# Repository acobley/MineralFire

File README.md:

View this project on [CADLAB.io](https://cadlab.io/node/793). 

# Volca_Pulse

Software for MineralFire Eurorack module.

This is an Arduino based programmable clock divider.  

NOTES
The Most up to date branch is "AltCounter"

The hardware design is in testing, do not use for production. 

The Software works, but is still under development.

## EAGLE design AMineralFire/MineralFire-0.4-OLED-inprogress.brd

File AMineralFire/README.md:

This is a development system, these are the eagle files for the Electronics.  They are still in test and are provided for information only.

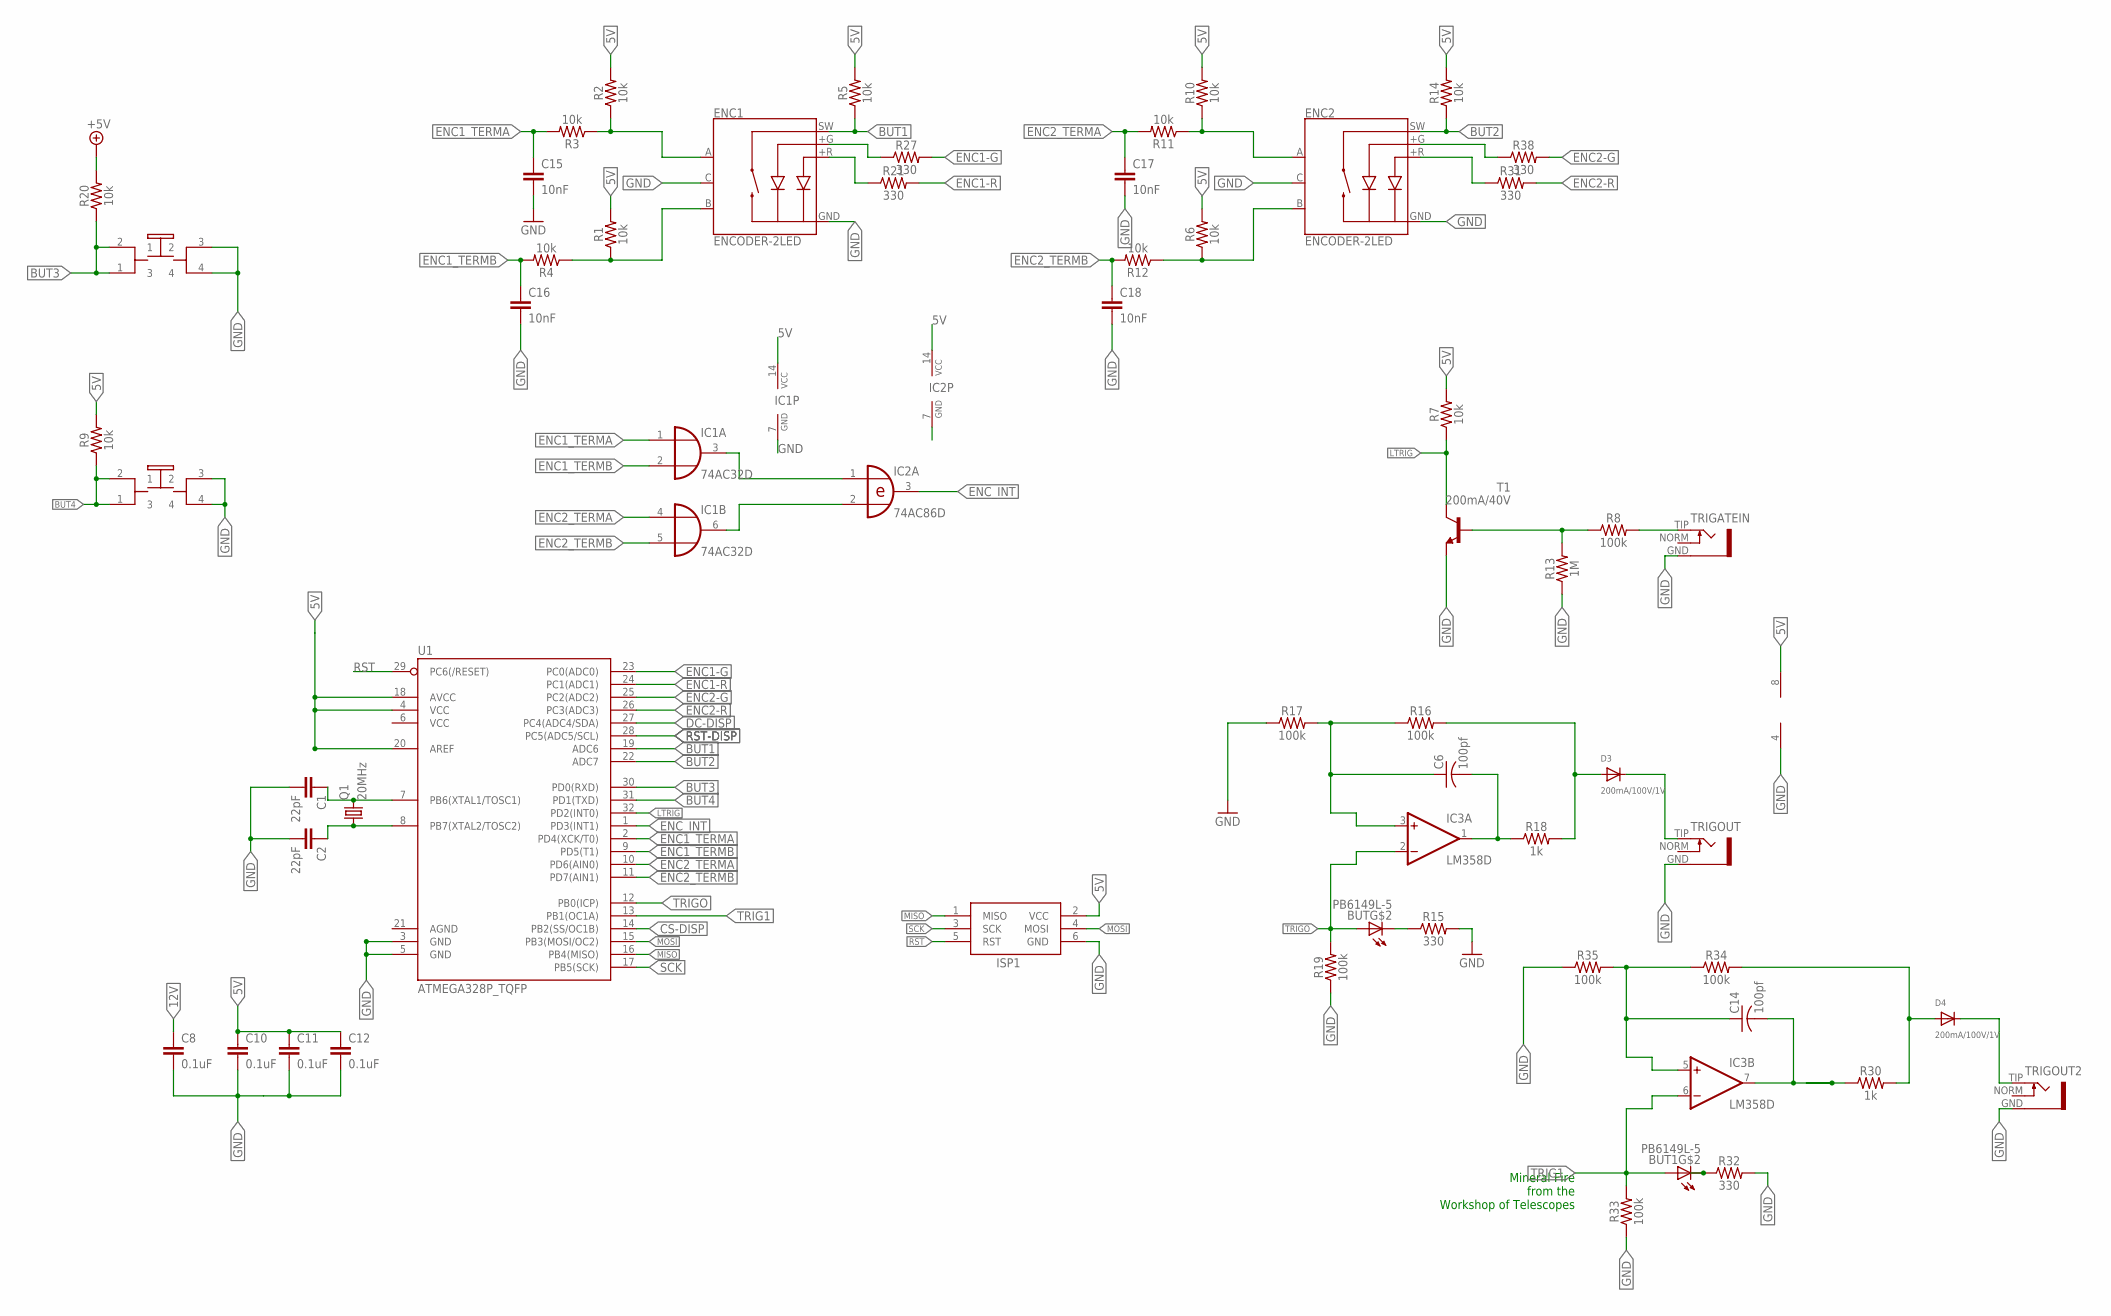
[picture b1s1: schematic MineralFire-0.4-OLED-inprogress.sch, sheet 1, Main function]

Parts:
BUT, BUT1: PB6149L-5; PB6149L
C1, C2: 22pF; 0603
C6, C14: 100pf; C0805K
C8, C10, C11, C12: 0.1uF; 0603
C15, C16, C17, C18: 10nF; 0603
D3, D4: 200mA/100V/1V; SMADIODE
ENC1, ENC2: ENCODER-2LED; ENCODER_LED_2
IC1: 74AC32D; SO14
IC2: 74AC86D; SO14
IC3: LM358D; SO08
ISP1: AVRISP-6; AVRISP
Q1: 20MHz; HC49UP
R1, R2, R3, R4, R5, R6, R7, R9, R10, R11, R12, R14, R20: 10k; 0603
R8, R16, R17, R19, R33, R34, R35: 100k; 0603
R13: 1M; 0603
R15, R21, R27, R31, R32, R38: 330; 0603
R18, R30: 1k; 0603
T1: 200mA/40V; SOT23-BEC
TRIGATEIN: S_JACK
TRIGOUT, TRIGOUT2: S_JACK
U1: ATMEGA328P_TQFP; TQFP32-08

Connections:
5V: C10.1, C11.1, C12.1, IC1.14 (VCC), IC2.14 (VCC), IC3.8 (V+), ISP1.2 (VCC), R1.2, R2.2, R5.2, R6.2, R7.2, R9.2, R10.2, R14.2, U1.4 (VCC), U1.18 (AVCC), U1.20 (AREF); also elsewhere on the board
12V: C8.1; also elsewhere on the board
+5V: R20.2
BUT1: ENC1.SW, R5.1, U1.19 (ADC6)
BUT2: ENC2.SW, R14.1, U1.22 (ADC7)
BUT3: BUT1.1 (3), BUT1.2 (1), R20.1, U1.30 (PD0(RXD))
BUT4: BUT.1 (3), BUT.2 (1), R9.1, U1.31 (PD1(TXD))
CS-DISP: U1.14 (PB2(SS/OC1B)); also elsewhere on the board
DC-DISP: U1.27 (PC4(ADC4/SDA)); also elsewhere on the board
ENC1-G: R27.2, U1.23 (PC0(ADC0))
ENC1-R: R21.2, U1.24 (PC1(ADC1))
ENC1_TERMA: C15.1, IC1.1 (I0), R3.2, U1.2 (PD4(XCK/T0))
ENC1_TERMB: C16.1, IC1.2 (I1), R4.2, U1.9 (PD5(T1))
ENC2-G: R38.2, U1.25 (PC2(ADC2))
ENC2-R: R31.2, U1.26 (PC3(ADC3))
ENC2_TERMA: C17.1, IC1.4 (I0), R11.2, U1.10 (PD6(AIN0))
ENC2_TERMB: C18.1, IC1.5 (I1), R12.2, U1.11 (PD7(AIN1))
ENC_INT: IC2.3 (O), U1.1 (PD3(INT1))
GND: BUT.3 (2), BUT.4, BUT1.3 (2), BUT1.4, C1.2, C2.2, C8.2, C10.2, C11.2, C12.2, C15.2, C16.2, C17.2, C18.2, ENC1.C, ENC1.GND (-), ENC2.C, ENC2.GND (-), IC1.7 (GND), IC2.7 (GND), IC3.4 (V-), ISP1.6 (GND), R13.1, R15.2, R17.1, R19.1, R32.2, R33.1, R35.1, T1.E, TRIGATEIN.GND, TRIGOUT.GND, TRIGOUT2.GND, U1.3 (GND), U1.5 (GND); also elsewhere on the board
LTRIG: R7.1, T1.C, U1.32 (PD2(INT0))
MISO: ISP1.1 (MISO), U1.16 (PB4(MISO))
MOSI: ISP1.4 (MOSI), U1.15 (PB3(MOSI/OC2)); also elsewhere on the board
unnamed: C1.1, Q1.2, U1.7 (PB6(XTAL1/TOSC1))
unnamed: C2.1, Q1.1, U1.8 (PB7(XTAL2/TOSC2))
unnamed: ENC1.+R, R21.1
unnamed: IC1.3 (O), IC2.1 (I0)
unnamed: IC1.6 (O), IC2.2 (I1)
unnamed: ENC1.A, R2.1, R3.1
unnamed: ENC1.B, R1.1, R4.1
unnamed: R8.1, R13.2, T1.B
unnamed: R8.2, TRIGATEIN.TIP
unnamed: C14.2, IC3.7 (OUT), R30.1
unnamed: BUT1.K (C), R32.1
unnamed: D4.A, R30.2, R34.2
unnamed: D4.C, TRIGOUT2.TIP
unnamed: C14.1, IC3.5 (+IN), R34.1, R35.2
unnamed: ENC2.A, R10.1, R11.1
unnamed: ENC2.B, R6.1, R12.1
unnamed: ENC1.+G, R27.1
unnamed: BUT.K (C), R15.1
unnamed: C6.1, IC3.3 (+IN), R16.1, R17.2
unnamed: C6.2, IC3.1 (OUT), R18.1
unnamed: D3.A, R16.2, R18.2
unnamed: ENC2.+G, R38.1
unnamed: ENC2.+R, R31.1
unnamed: D3.C, TRIGOUT.TIP
RST: ISP1.5 (RST), U1.29 (PC6(/RESET))
RST-DISP: U1.28 (PC5(ADC5/SCL)); also elsewhere on the board
SCK: ISP1.3 (SCK), U1.17 (PB5(SCK)); also elsewhere on the board
TRIG1: BUT1.A, IC3.6 (-IN), R33.2, U1.13 (PB1(OC1A))
TRIGO: BUT.A, IC3.2 (-IN), R19.2, U1.12 (PB0(ICP))

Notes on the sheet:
Mineral Fire from the Workshop of Telescopes

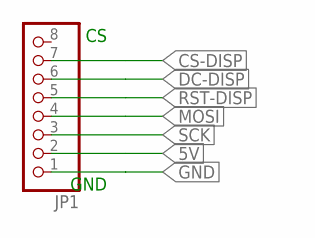
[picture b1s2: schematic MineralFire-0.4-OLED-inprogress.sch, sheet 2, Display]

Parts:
JP1: MICROBUILDER_HEADER-1X8ROUND; MICROBUILDER_1X08_ROUND

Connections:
5V: JP1.2; also elsewhere on the board
CS-DISP: JP1.7; also elsewhere on the board
DC-DISP: JP1.6; also elsewhere on the board
GND: JP1.1; also elsewhere on the board
MOSI: JP1.4; also elsewhere on the board
RST-DISP: JP1.5; also elsewhere on the board
SCK: JP1.3; also elsewhere on the board

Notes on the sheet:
GND

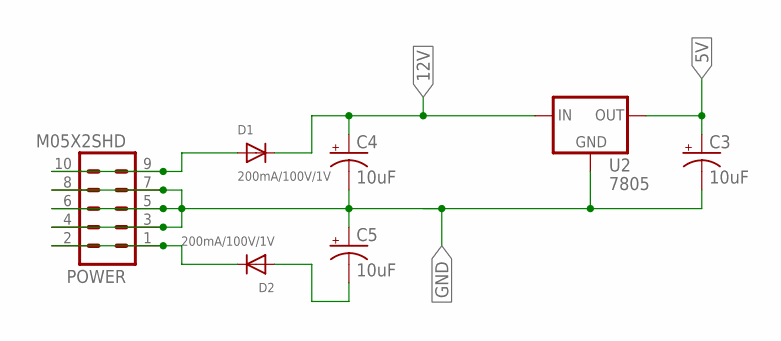
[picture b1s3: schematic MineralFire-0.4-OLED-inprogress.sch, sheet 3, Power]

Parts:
C3, C4, C5: 10uF; 153CLV-0505
D1, D2: 200mA/100V/1V; SMADIODE
POWER: M05X2SHD; 2X5-SHROUDED
U2: 7805; V-REG

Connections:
5V: C3.+, U2.3 (OUT); also elsewhere on the board
12V: C4.+, D1.C, U2.1 (IN); also elsewhere on the board
GND: C3.-, C4.-, C5.+, POWER.3, POWER.4, POWER.5, POWER.6, POWER.7, POWER.8, U2.4 (GND); also elsewhere on the board
unnamed: D1.A, POWER.9, POWER.10
unnamed: D2.C, POWER.1, POWER.2
unnamed: C5.-, D2.A

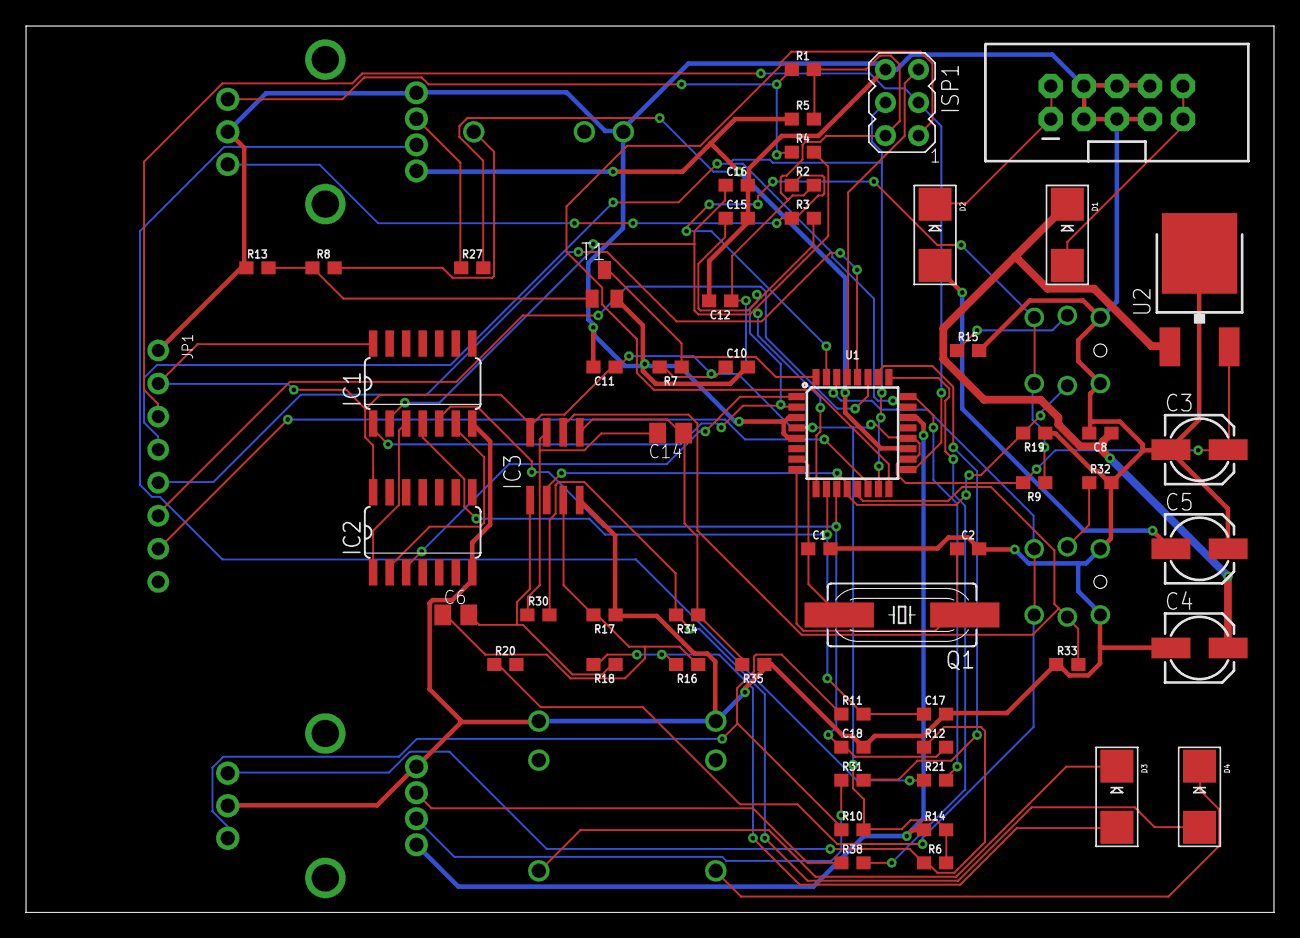
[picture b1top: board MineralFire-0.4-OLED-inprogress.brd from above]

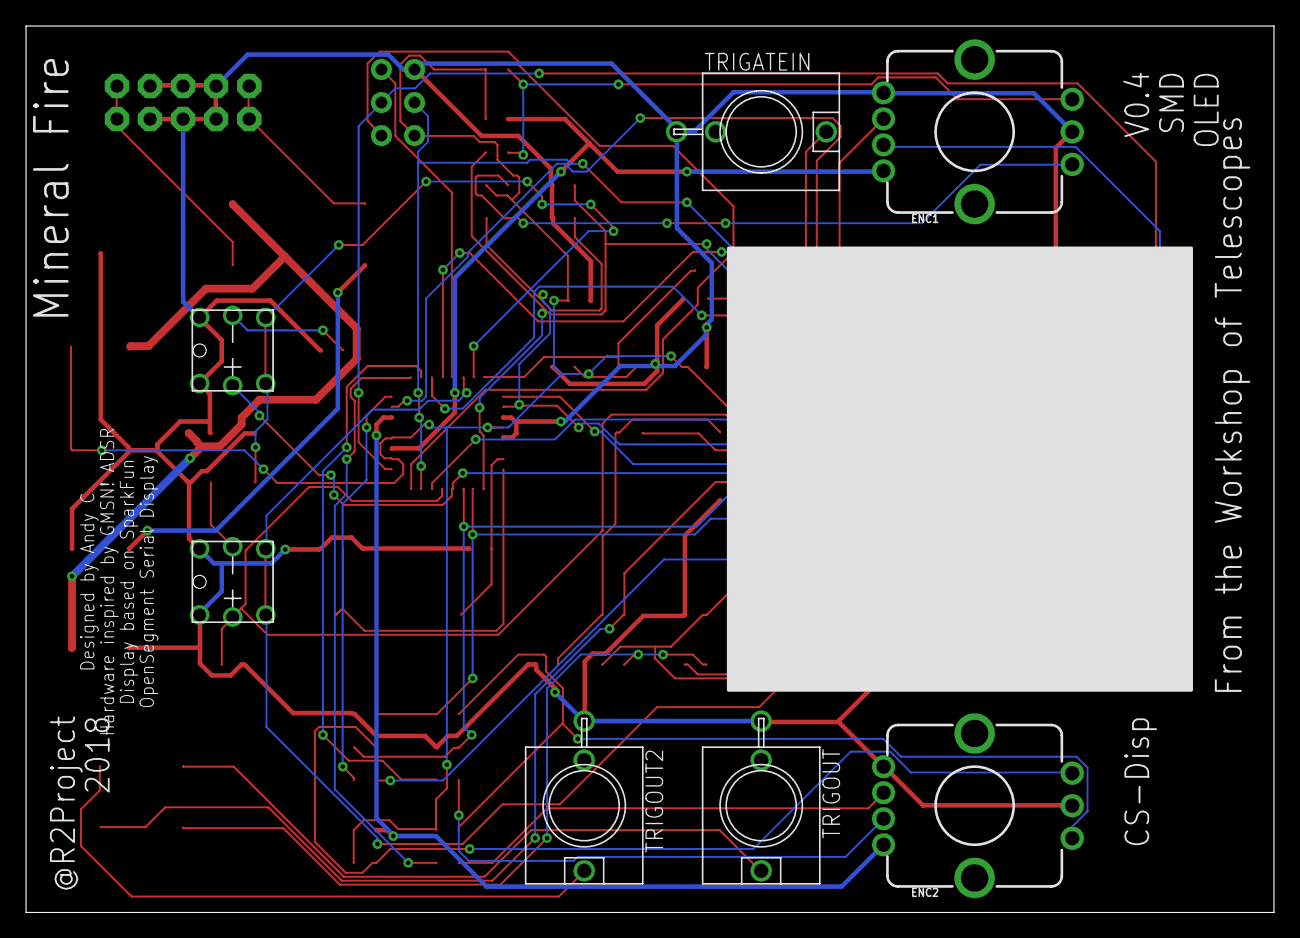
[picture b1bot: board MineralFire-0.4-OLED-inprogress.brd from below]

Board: 2 copper layers, 95.9 x 68.1 mm, 65 parts (7 on the bottom side), 53 nets.

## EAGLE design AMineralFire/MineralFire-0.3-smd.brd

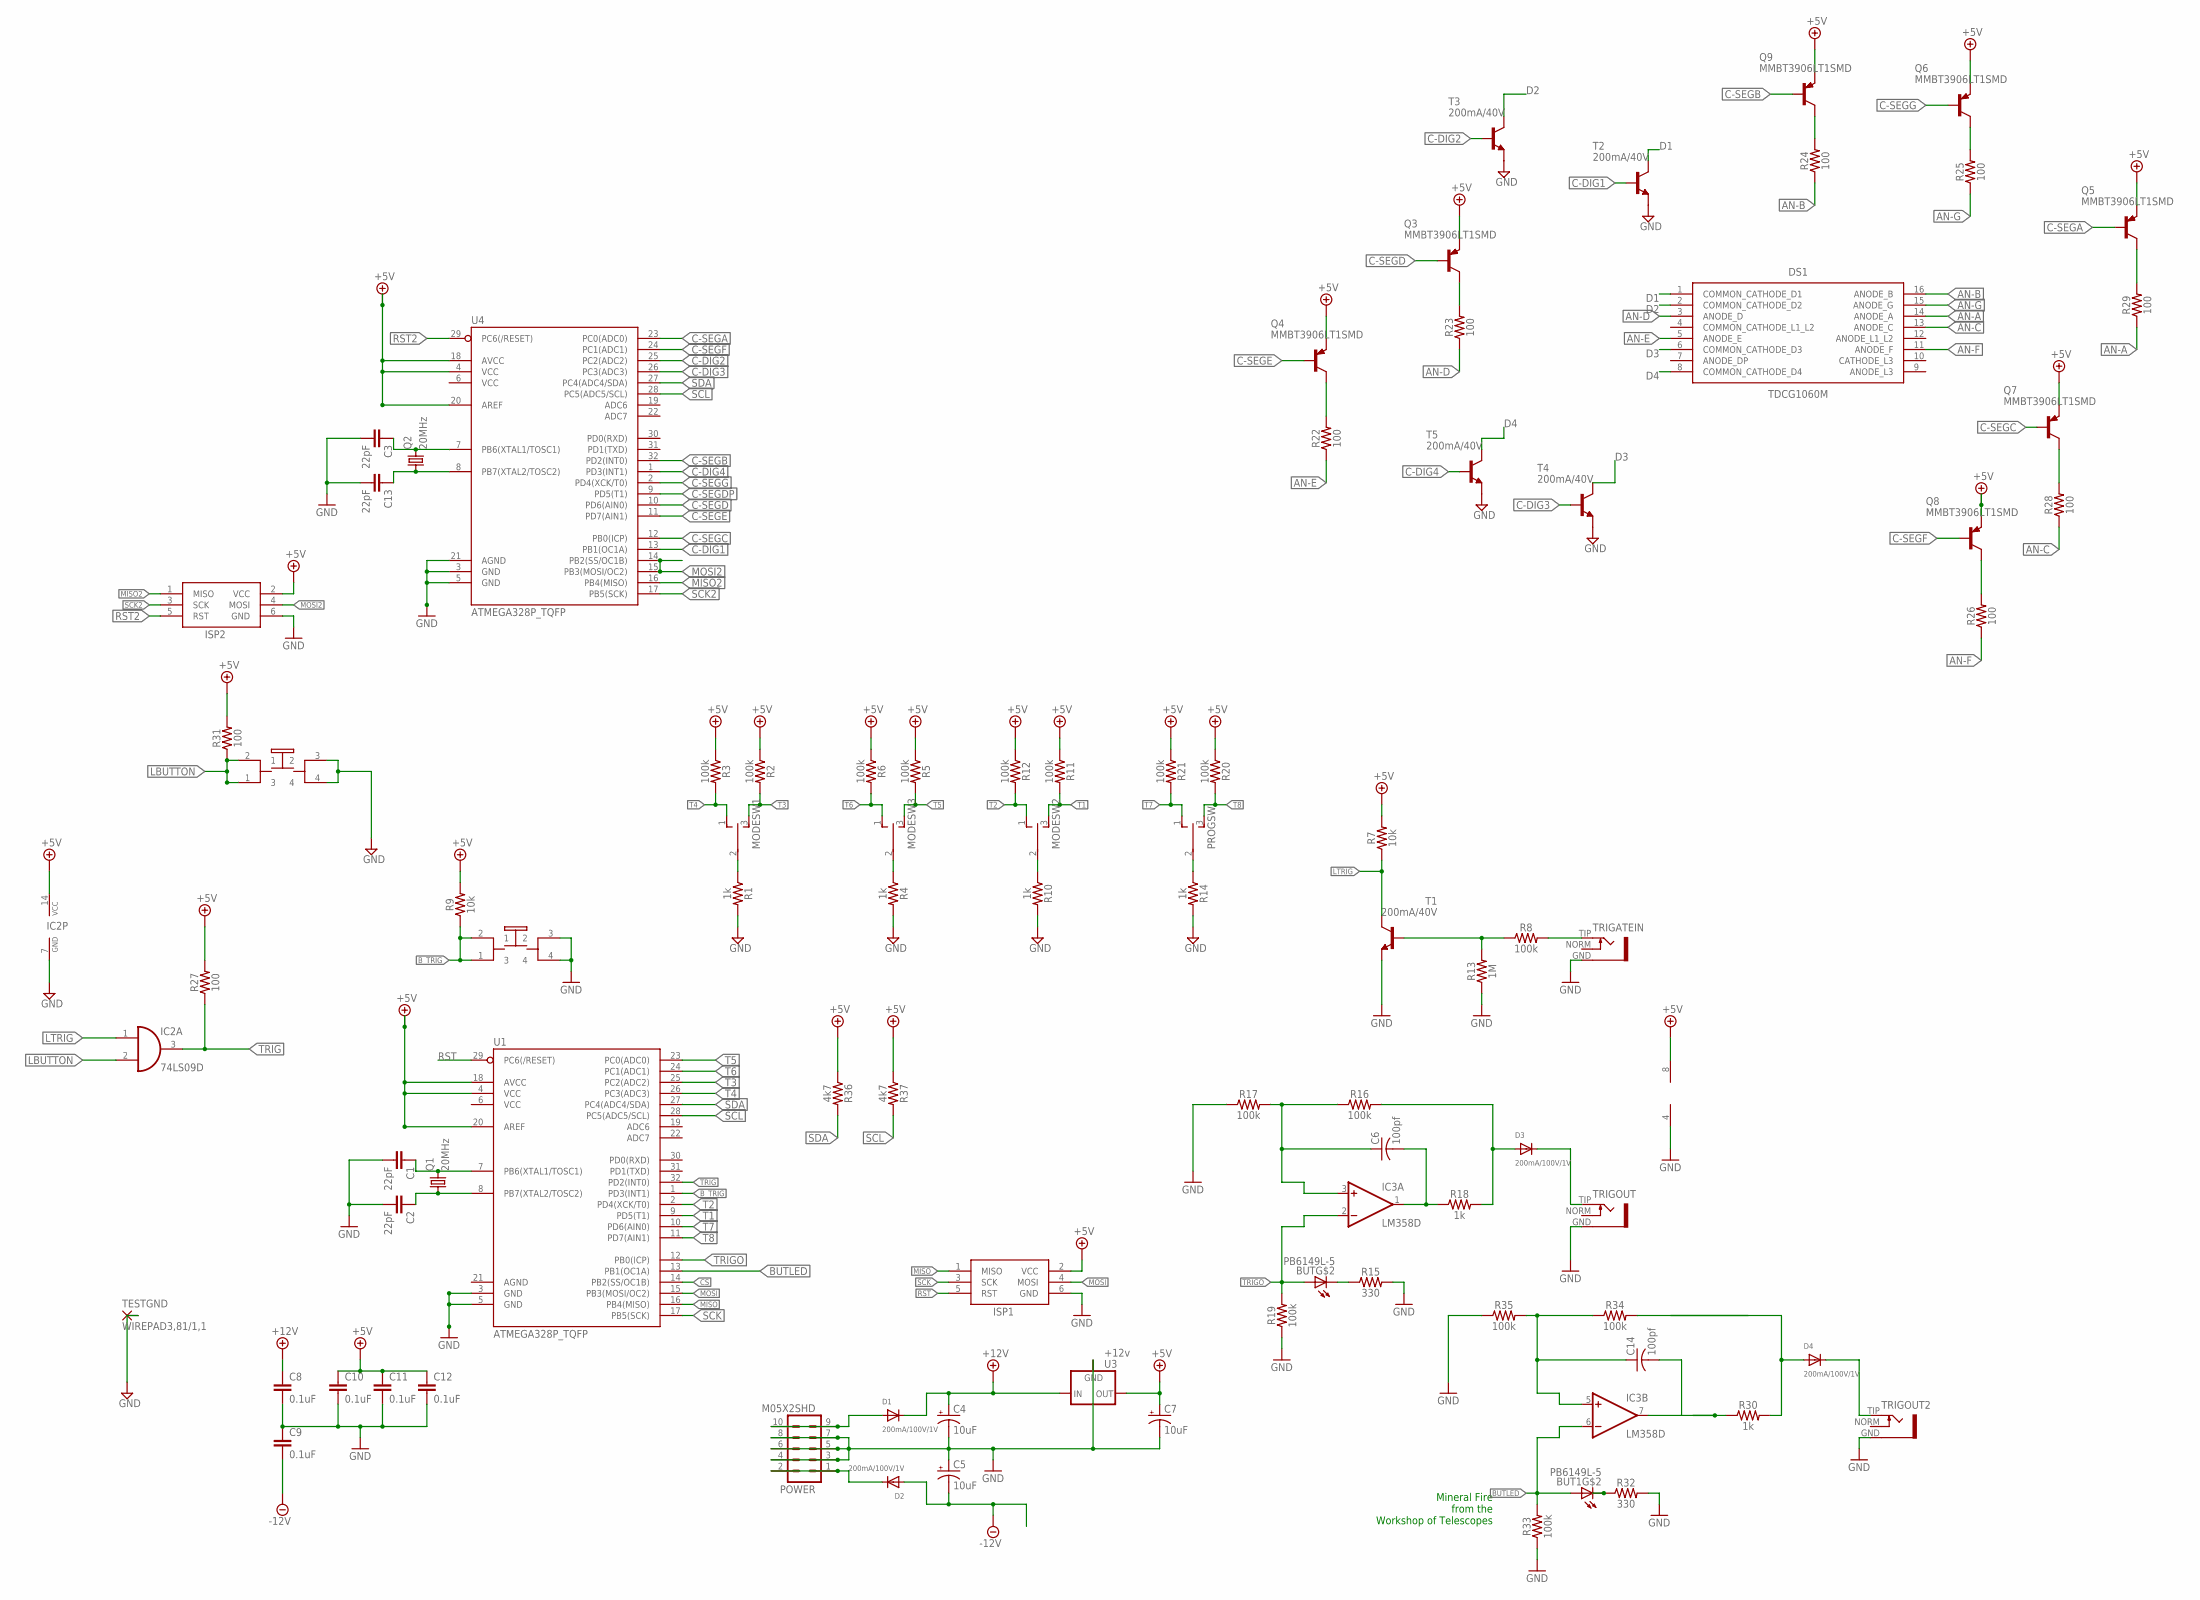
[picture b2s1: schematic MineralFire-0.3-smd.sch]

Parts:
BUT, BUT1: PB6149L-5; PB6149L
C1, C2, C3, C13: 22pF; 0603
C4, C5, C7: 10uF; 153CLV-0505
C6, C14: 100pf; C0805K
C8, C9, C10, C11, C12: 0.1uF; 0603
D1, D2, D3, D4: 200mA/100V/1V; SMADIODE
DS1: TDCG1060M; DIPS1016W50P254L4020H700Q16N
IC2: 74LS09D; SO14
IC3: LM358D; SO08
ISP1, ISP2: AVRISP-6; AVRISP
MODESW1, MODESW2, MODESW3: TOGGLE_ON_OFF_ON
POWER: M05X2SHD; 2X5-SHROUDED
PROGSW: TOGGLE_ON_OFF_ON
Q1, Q2: 20MHz; HC49UP
Q3, Q4, Q5, Q6, Q7, Q8, Q9: MMBT3906LT1SMD; SOT23-BEC
R1, R4, R10, R14, R18, R30: 1k; 0603
R2, R3, R5, R6, R8, R11, R12, R16, R17, R19, R20, R21, R33, R34, R35: 100k; 0603
R7, R9: 10k; 0603
R13: 1M; 0603
R15, R32: 330; 0603
R22, R23, R24, R25, R26, R27, R28, R29, R31: 100; 0603
R36, R37: 4k7; 0603
T1, T2, T3, T4, T5: 200mA/40V; SOT23-BEC
TESTGND: WIREPAD3,81/1,1; 3,81/1,1
TRIGATEIN: S_JACK
TRIGOUT, TRIGOUT2: S_JACK
U1, U4: ATMEGA328P_TQFP; TQFP32-08
U3: +12v; TO-252

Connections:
+5V: C7.+, C10.1, C11.1, C12.1, IC2.14 (VCC), IC3.8 (V+), ISP1.2 (VCC), ISP2.2 (VCC), Q3.E, Q4.E, Q5.E, Q6.E, Q7.E, Q8.E, Q9.E, R2.1, R3.1, R5.1, R6.1, R7.2, R9.2, R11.1, R12.1, R20.1, R21.1, R27.2, R31.2, R36.1, R37.1, U1.4 (VCC), U1.18 (AVCC), U1.20 (AREF), U3.2 (OUT), U4.4 (VCC), U4.18 (AVCC), U4.20 (AREF)
+12V: C4.+, C8.1, D1.C, U3.1 (IN)
-12V: C5.-, C9.2, D2.A
AN-A: DS1.14 (ANODE_A), R29.1
AN-B: DS1.16 (ANODE_B), R24.1
AN-C: DS1.13 (ANODE_C), R28.1
AN-D: DS1.3 (ANODE_D), R23.1
AN-E: DS1.5 (ANODE_E), R22.1
AN-F: DS1.11 (ANODE_F), R26.1
AN-G: DS1.15 (ANODE_G), R25.1
BUTLED: BUT1.A, IC3.6 (-IN), R33.2, U1.13 (PB1(OC1A))
B_TRIG: BUT.1 (3), BUT.2 (1), R9.1, U1.1 (PD3(INT1))
C-DIG1: T2.B, U4.13 (PB1(OC1A))
C-DIG2: T3.B, U4.25 (PC2(ADC2))
C-DIG3: T4.B, U4.26 (PC3(ADC3))
C-DIG4: T5.B, U4.1 (PD3(INT1))
C-SEGA: Q5.B, U4.23 (PC0(ADC0))
C-SEGB: Q9.B, U4.32 (PD2(INT0))
C-SEGC: Q7.B, U4.12 (PB0(ICP))
C-SEGD: Q3.B, U4.10 (PD6(AIN0))
C-SEGDP: U4.9 (PD5(T1))
C-SEGE: Q4.B, U4.11 (PD7(AIN1))
C-SEGF: Q8.B, U4.24 (PC1(ADC1))
C-SEGG: Q6.B, U4.2 (PD4(XCK/T0))
CS: U1.14 (PB2(SS/OC1B))
D1: DS1.1 (COMMON_CATHODE_D1), T2.C
D2: DS1.2 (COMMON_CATHODE_D2), T3.C
D3: DS1.6 (COMMON_CATHODE_D3), T4.C
D4: DS1.8 (COMMON_CATHODE_D4), T5.C
GND: BUT.3 (2), BUT.4, BUT1.3 (2), BUT1.4, C1.2, C2.2, C3.2, C4.-, C5.+, C7.-, C8.2, C9.1, C10.2, C11.2, C12.2, C13.2, IC2.7 (GND), IC3.4 (V-), ISP1.6 (GND), ISP2.6 (GND), POWER.3, POWER.4, POWER.5, POWER.6, POWER.7, POWER.8, R1.2, R4.2, R10.2, R13.1, R14.2, R15.2, R17.1, R19.1, R32.2, R33.1, R35.1, T1.E, T2.E, T3.E, T4.E, T5.E, TESTGND.1, TRIGATEIN.GND, TRIGOUT.GND, TRIGOUT2.GND, U1.3 (GND), U1.5 (GND), U3.3 (GND), U4.3 (GND), U4.5 (GND), U4.21 (AGND)
LBUTTON: BUT1.1 (3), BUT1.2 (1), IC2.2 (I1), R31.1
LTRIG: IC2.1 (I0), R7.1, T1.C
MISO: ISP1.1 (MISO), U1.16 (PB4(MISO))
MISO2: ISP2.1 (MISO), U4.16 (PB4(MISO))
MOSI: ISP1.4 (MOSI), U1.15 (PB3(MOSI/OC2))
MOSI2: ISP2.4 (MOSI), U4.14 (PB2(SS/OC1B)), U4.15 (PB3(MOSI/OC2))
unnamed: C1.1, Q1.2, U1.7 (PB6(XTAL1/TOSC1))
unnamed: C2.1, Q1.1, U1.8 (PB7(XTAL2/TOSC2))
unnamed: MODESW1.2, R1.1
unnamed: MODESW3.2, R4.1
unnamed: Q4.C, R22.2
unnamed: PROGSW.2, R14.1
unnamed: C3.1, Q2.2, U4.7 (PB6(XTAL1/TOSC1))
unnamed: C13.1, Q2.1, U4.8 (PB7(XTAL2/TOSC2))
unnamed: D1.A, POWER.9, POWER.10
unnamed: D2.C, POWER.1, POWER.2
unnamed: Q3.C, R23.2
unnamed: MODESW2.2, R10.1
unnamed: Q9.C, R24.2
unnamed: Q8.C, R26.2
unnamed: R8.1, R13.2, T1.B
unnamed: Q7.C, R28.2
unnamed: Q6.C, R25.2
unnamed: R8.2, TRIGATEIN.TIP
unnamed: IC3.7 (OUT), R30.1
unnamed: Q5.C, R29.2
unnamed: BUT1.K (C), R32.1
unnamed: D4.A, R30.2
unnamed: D4.C, TRIGOUT2.TIP
unnamed: C14.1, IC3.5 (+IN), R34.1, R35.2
unnamed: BUT.K (C), R15.1
unnamed: C6.1, IC3.3 (+IN), R16.1, R17.2
unnamed: C6.2, IC3.1 (OUT), R18.1
unnamed: D3.A, R16.2, R18.2
unnamed: D3.C, TRIGOUT.TIP
RST: ISP1.5 (RST), U1.29 (PC6(/RESET))
RST2: ISP2.5 (RST), U4.29 (PC6(/RESET))
SCK: ISP1.3 (SCK), U1.17 (PB5(SCK))
SCK2: ISP2.3 (SCK), U4.17 (PB5(SCK))
SCL: R37.2, U1.28 (PC5(ADC5/SCL)), U4.28 (PC5(ADC5/SCL))
SDA: R36.2, U1.27 (PC4(ADC4/SDA)), U4.27 (PC4(ADC4/SDA))
T1: MODESW2.3 (S), R11.2, U1.9 (PD5(T1))
T2: MODESW2.1 (O), R12.2, U1.2 (PD4(XCK/T0))
T3: MODESW1.3 (S), R2.2, U1.25 (PC2(ADC2))
T4: MODESW1.1 (O), R3.2, U1.26 (PC3(ADC3))
T5: MODESW3.3 (S), R5.2, U1.23 (PC0(ADC0))
T6: MODESW3.1 (O), R6.2, U1.24 (PC1(ADC1))
T7: PROGSW.1 (O), R21.2, U1.10 (PD6(AIN0))
T8: PROGSW.3 (S), R20.2, U1.11 (PD7(AIN1))
TRIG: IC2.3 (O), R27.1, U1.32 (PD2(INT0))
TRIGO: BUT.A, IC3.2 (-IN), R19.2, U1.12 (PB0(ICP))

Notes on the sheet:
Mineral Fire from the Workshop of Telescopes

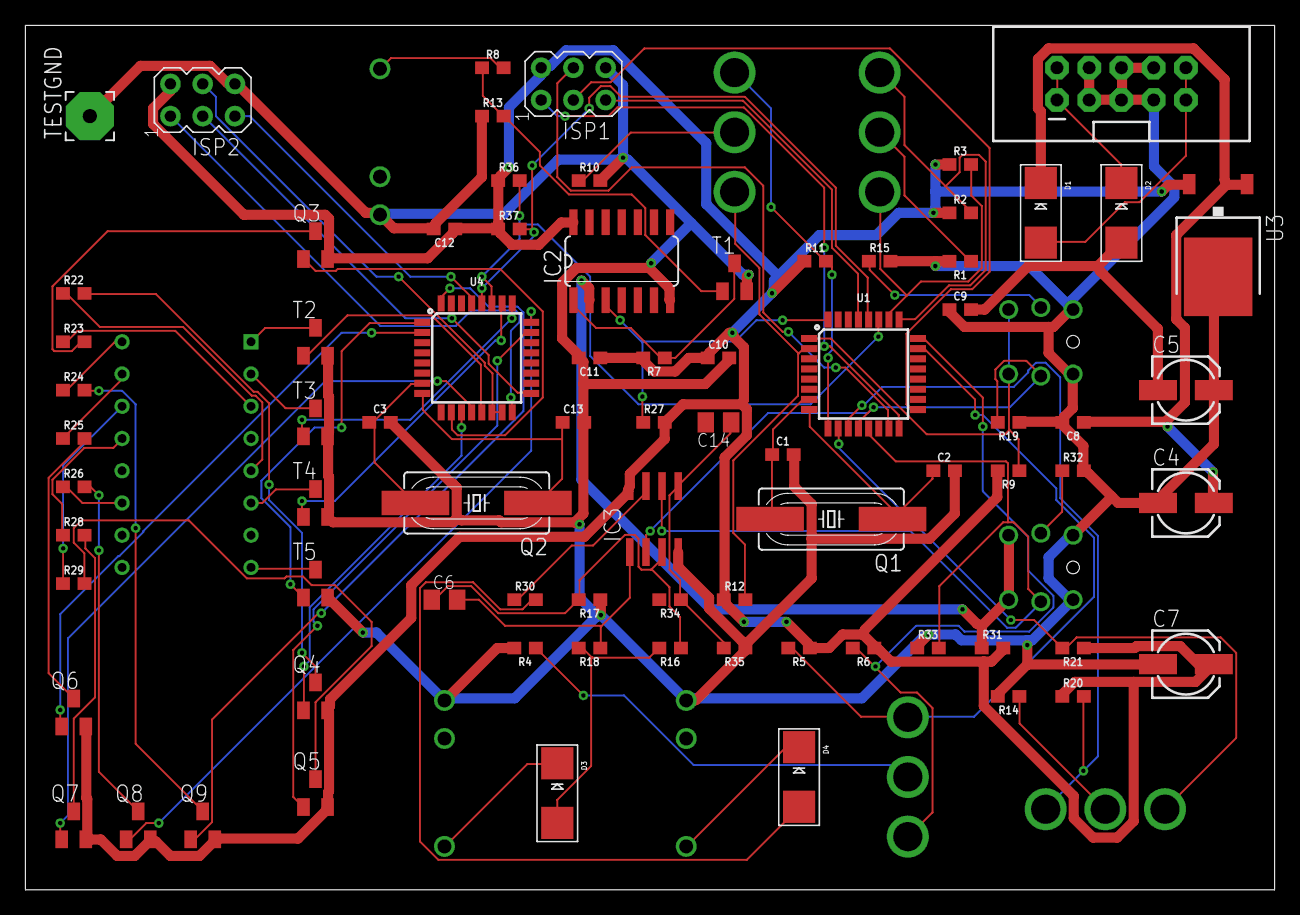
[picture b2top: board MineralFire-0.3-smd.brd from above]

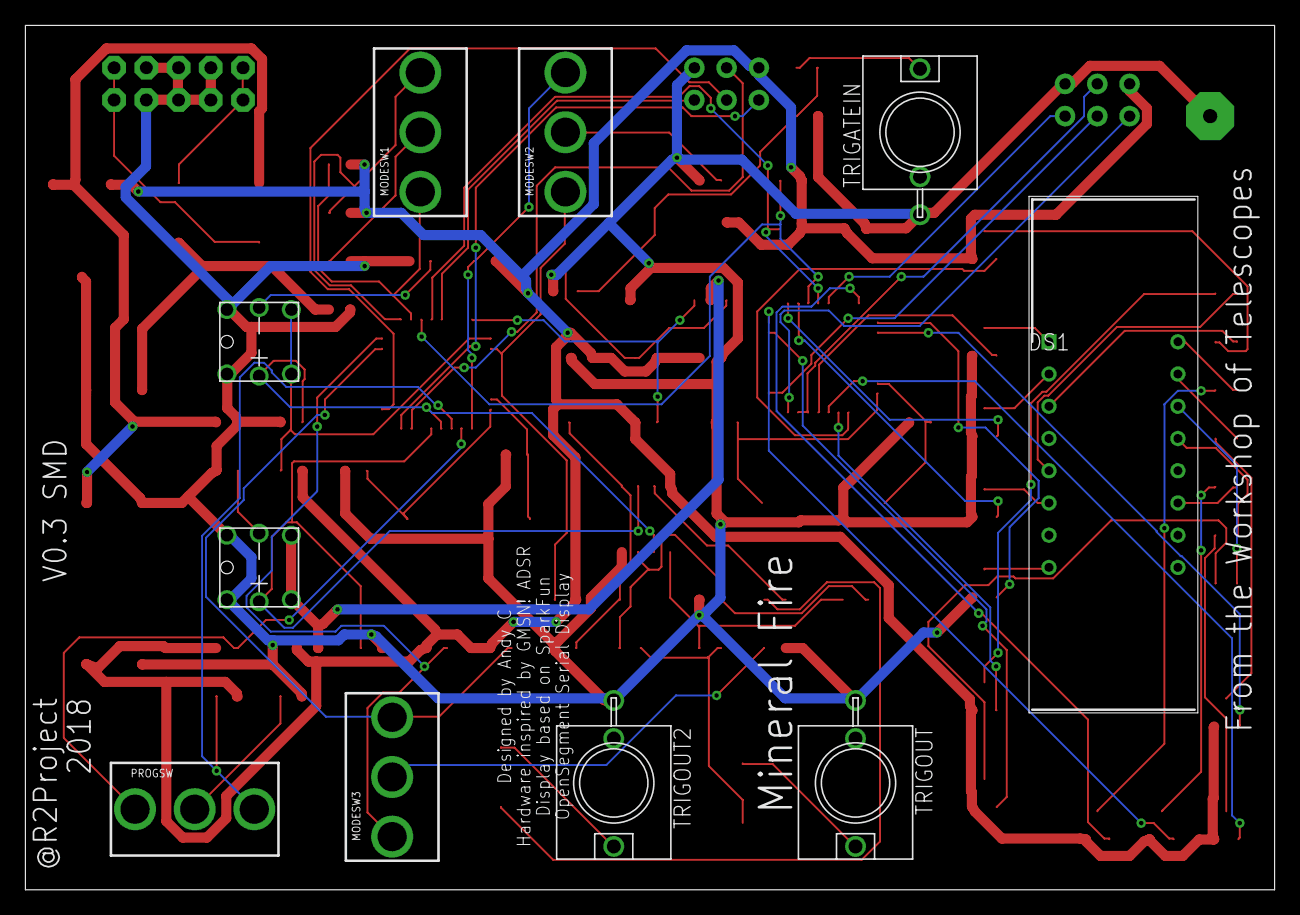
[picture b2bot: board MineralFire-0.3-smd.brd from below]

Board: 2 copper layers, 98.4 x 68.1 mm, 88 parts (10 on the bottom side), 79 nets.

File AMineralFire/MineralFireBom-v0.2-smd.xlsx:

Part | Value | Device | Package | Description | 3D_PACKAGE | ALLIED_NUMBER | DESCRIPTION | HEIGHT | MANUFACTURER_NAME | MANUFACTURER_PART_NUMBER | MF | MPN | OC_FARNELL | OC_NEWARK | OTHER_PART_NUMBER | PROD_ID | RS_PART_NUMBER | SUPPLIER_NAME | VALUE
C3 | 22pF | 22PF-0603-50V-5% | 603 | 22pF ceramic capacitors |  |  |  |  |  |  |  |  |  |  |  | CAP-07876 |  |  | 22pF
C4 | 10¬µF | 10UF-POLAR-EIA6032-25V-10% | EIA6032-NOM | 10.0¬µF polarized capacitors |  |  |  |  |  |  |  |  |  |  |  | CAP-12984 |  |  | 10¬µF
C5 | 10¬µF | 10UF-POLAR-EIA6032-25V-10% | EIA6032-NOM | 10.0¬µF polarized capacitors |  |  |  |  |  |  |  |  |  |  |  | CAP-12984 |  |  | 10¬µF
C6 | 100pf | C-EU01005 | C01005 | CAPACITOR, European symbol
C7 | 10¬µF | 10UF-POLAR-EIA6032-25V-10% | EIA6032-NOM | 10.0¬µF polarized capacitors |  |  |  |  |  |  |  |  |  |  |  | CAP-12984 |  |  | 10¬µF
C8 | 0.1uF | 0.1UF-0603-25V-5% | 603 | 0.1¬µF ceramic capacitors |  |  |  |  |  |  |  |  |  |  |  | CAP-08604 |  |  | 0.1uF
C9 | 0.1uF | 0.1UF-0603-25V-5% | 603 | 0.1¬µF ceramic capacitors |  |  |  |  |  |  |  |  |  |  |  | CAP-08604 |  |  | 0.1uF
C10 | 0.1uF | 0.1UF-0603-25V-5% | 603 | 0.1¬µF ceramic capacitors |  |  |  |  |  |  |  |  |  |  |  | CAP-08604 |  |  | 0.1uF
C11 | 0.1uF | 0.1UF-0603-25V-5% | 603 | 0.1¬µF ceramic capacitors |  |  |  |  |  |  |  |  |  |  |  | CAP-08604 |  |  | 0.1uF
C12 | 0.1uF | 0.1UF-0603-25V-5% | 603 | 0.1¬µF ceramic capacitors |  |  |  |  |  |  |  |  |  |  |  | CAP-08604 |  |  | 0.1uF
C13 | 22pF | 22PF-0603-50V-5% | 603 | 22pF ceramic capacitors |  |  |  |  |  |  |  |  |  |  |  | CAP-07876 |  |  | 22pF
C14 | 22pF | 22PF-0603-50V-5% | 603 | 22pF ceramic capacitors |  |  |  |  |  |  |  |  |  |  |  | CAP-07876 |  |  | 22pF
C15 | 22pF | 22PF-0603-50V-5% | 603 | 22pF ceramic capacitors |  |  |  |  |  |  |  |  |  |  |  | CAP-07876 |  |  | 22pF
D1 | 250mA/100V | DIODE-BAS16J | SOD-323 | Diode |  |  |  |  |  |  |  |  |  |  |  | DIO-09646 |  |  | 250mA/100V
D2 | 250mA/100V | DIODE-BAS16J | SOD-323 | Diode |  |  |  |  |  |  |  |  |  |  |  | DIO-09646 |  |  | 250mA/100V
D3 | 250mA/100V | DIODE-BAS16J | SOD-323 | Diode |  |  |  |  |  |  |  |  |  |  |  | DIO-09646 |  |  | 250mA/100V
DS1 | TDCG1060M | TDCG1060M | DIPS1016W50P254L4020H700Q16N | VISHAY - TDCG1060M - DISPLAY, SEVEN SEGMENT, 10MM, GREEN |  |  | VISHAY - TDCG1060M - DISPLAY, SEVEN SEGMENT, 10MM, GREEN | 7mm | Vishay | TDCG1060M |  |  |  |  |  |  | 8187530P | RS
IC2 | OP-AMP | OPAMP-DUALU | SO08 | Generic op-amp footprint |  |  |  |  |  |  |  |  |  |  |  | NA-XXXXX |  |  | OP-AMP
IC3 | 7432D | 7432D | SO14 | Quad 2-input OR gate
Q2 | 20MHz | CRYSTALHC49UP | HC49UP | CRYSTAL |  |  |  |  |  |  |  |  | unknown | unknown
Q3 | 200mA/40V | TRANS_PNP-PMBT3906|MMBT3906L | SOT23-3 | PNP transistor |  |  |  |  |  |  |  |  |  |  |  | TRANS-08052 |  |  | 200mA/40V
Q4 | 200mA/40V | TRANS_PNP-PMBT3906|MMBT3906L | SOT23-3 | PNP transistor |  |  |  |  |  |  |  |  |  |  |  | TRANS-08052 |  |  | 200mA/40V
Q5 | 200mA/40V | TRANS_PNP-PMBT3906|MMBT3906L | SOT23-3 | PNP transistor |  |  |  |  |  |  |  |  |  |  |  | TRANS-08052 |  |  | 200mA/40V
Q6 | 200mA/40V | TRANS_PNP-PMBT3906|MMBT3906L | SOT23-3 | PNP transistor |  |  |  |  |  |  |  |  |  |  |  | TRANS-08052 |  |  | 200mA/40V
Q7 | 200mA/40V | TRANS_PNP-PMBT3906|MMBT3906L | SOT23-3 | PNP transistor |  |  |  |  |  |  |  |  |  |  |  | TRANS-08052 |  |  | 200mA/40V
Q8 | 200mA/40V | TRANS_PNP-PMBT3906|MMBT3906L | SOT23-3 | PNP transistor |  |  |  |  |  |  |  |  |  |  |  | TRANS-08052 |  |  | 200mA/40V
Q9 | 200mA/40V | TRANS_PNP-PMBT3906|MMBT3906L | SOT23-3 | PNP transistor |  |  |  |  |  |  |  |  |  |  |  | TRANS-08052 |  |  | 200mA/40V
Q10 | 20MHz | CRYSTALHC49UP | HC49UP | CRYSTAL |  |  |  |  |  |  |  |  | unknown | unknown
R1 | 1k | 1KOHM-0603-1/10W-1% | 603 | 1kŒ© resistor |  |  |  |  |  |  |  |  |  |  |  | RES-07856 |  |  | 1k
R2 | 100k | 100KOHM-0603-1/10W-1% | 603 | 100kŒ© resistor |  |  |  |  |  |  |  |  |  |  |  | RES-07828 |  |  | 100k
R3 | 100k | 100KOHM-0603-1/10W-1% | 603 | 100kŒ© resistor |  |  |  |  |  |  |  |  |  |  |  | RES-07828 |  |  | 100k
R4 | 1k | 1KOHM-0603-1/10W-1% | 603 | 1kŒ© resistor |  |  |  |  |  |  |  |  |  |  |  | RES-07856 |  |  | 1k
R5 | 100k | 100KOHM-0603-1/10W-1% | 603 | 100kŒ© resistor |  |  |  |  |  |  |  |  |  |  |  | RES-07828 |  |  | 100k
R6 | 100K | 100KOHM-0402-1/16W-1% | 402 | 100kŒ© resistor |  |  |  |  |  |  |  |  |  |  |  | RES-13495 |  |  | 100K
R7 | 10k | 10KOHM-0603-1/10W-1% | 603 | 10kŒ© resistor |  |  |  |  |  |  |  |  |  |  |  | RES-00824 |  |  | 10k
R8 | 100k | 100KOHM-0603-1/10W-1% | 603 | 100kŒ© resistor |  |  |  |  |  |  |  |  |  |  |  | RES-07828 |  |  | 100k
R9 | 10k | 10KOHM-0603-1/10W-1% | 603 | 10kŒ© resistor |  |  |  |  |  |  |  |  |  |  |  | RES-00824 |  |  | 10k
R10 | 1k | 1KOHM-0603-1/10W-1% | 603 | 1kŒ© resistor |  |  |  |  |  |  |  |  |  |  |  | RES-07856 |  |  | 1k
R11 | 100k | 100KOHM-0603-1/10W-1% | 603 | 100kŒ© resistor |  |  |  |  |  |  |  |  |  |  |  | RES-07828 |  |  | 100k
R12 | 100k | 100KOHM-0603-1/10W-1% | 603 | 100kŒ© resistor |  |  |  |  |  |  |  |  |  |  |  | RES-07828 |  |  | 100k
R13 | 1M | 1MOHM-0603-1/4W-5% | 603 | 1MŒ© resistor |  |  |  |  |  |  |  |  |  |  |  | RES-07868 |  |  | 1M
R14 | 1k | 1KOHM-0603-1/10W-1% | 603 | 1kŒ© resistor |  |  |  |  |  |  |  |  |  |  |  | RES-07856 |  |  | 1k
R15 | 330 | 330OHM-0603-1/10W-1% | 603 | 330Œ© resistor |  |  |  |  |  |  |  |  |  |  |  | RES-00818 |  |  | 330
R16 | 100k | 100KOHM-0603-1/10W-1% | 603 | 100kŒ© resistor |  |  |  |  |  |  |  |  |  |  |  | RES-07828 |  |  | 100k
R17 | 100k | 100KOHM-0603-1/10W-1% | 603 | 100kŒ© resistor |  |  |  |  |  |  |  |  |  |  |  | RES-07828 |  |  | 100k
R18 | 1k | 1KOHM-0603-1/10W-1% | 603 | 1kŒ© resistor |  |  |  |  |  |  |  |  |  |  |  | RES-07856 |  |  | 1k
R19 | 100k | 100KOHM-0603-1/10W-1% | 603 | 100kŒ© resistor |  |  |  |  |  |  |  |  |  |  |  | RES-07828 |  |  | 100k
R20 | 100k | 100KOHM-0603-1/10W-1% | 603 | 100kŒ© resistor |  |  |  |  |  |  |  |  |  |  |  | RES-07828 |  |  | 100k
R21 | 100k | 100KOHM-0603-1/10W-1% | 603 | 100kŒ© resistor |  |  |  |  |  |  |  |  |  |  |  | RES-07828 |  |  | 100k
R22 | 68OHM-0603-1/10W-1% | 68OHM-0603-1/10W-1% | 603 | 68Œ© resistor
R23 | 68OHM-0603-1/10W-1% | 68OHM-0603-1/10W-1% | 603 | 68Œ© resistor
R24 | 68OHM-0603-1/10W-1% | 68OHM-0603-1/10W-1% | 603 | 68Œ© resistor
R25 | 68OHM-0603-1/10W-1% | 68OHM-0603-1/10W-1% | 603 | 68Œ© resistor
R26 | 68OHM-0603-1/10W-1% | 68OHM-0603-1/10W-1% | 603 | 68Œ© resistor
R27 | 100k | 100KOHM-0603-1/10W-1% | 603 | 100kŒ© resistor |  |  |  |  |  |  |  |  |  |  |  | RES-07828 |  |  | 100k
R28 | 68OHM-0603-1/10W-1% | 68OHM-0603-1/10W-1% | 603 | 68Œ© resistor
R29 | 68OHM-0603-1/10W-1% | 68OHM-0603-1/10W-1% | 603 | 68Œ© resistor
T1 | 600mA/40V | TRANS_NPN-MMBT2222AL | SOT23-3 | NPN transistor |  |  |  |  |  |  |  |  |  |  |  | TRANS-08049 |  |  | 600mA/40V
T2 | 600mA/40V | TRANS_NPN-MMBT2222AL | SOT23-3 | NPN transistor |  |  |  |  |  |  |  |  |  |  |  | TRANS-08049 |  |  | 600mA/40V
T3 | 600mA/40V | TRANS_NPN-MMBT2222AL | SOT23-3 | NPN transistor |  |  |  |  |  |  |  |  |  |  |  | TRANS-08049 |  |  | 600mA/40V
T4 | 600mA/40V | TRANS_NPN-MMBT2222AL | SOT23-3 | NPN transistor |  |  |  |  |  |  |  |  |  |  |  | TRANS-08049 |  |  | 600mA/40V
T5 | 600mA/40V | TRANS_NPN-MMBT2222AL | SOT23-3 | NPN transistor |  |  |  |  |  |  |  |  |  |  |  | TRANS-08049 |  |  | 600mA/40V
U3 | +12v | V_REG_78XX7812 | TO-252 | Voltage Regulator |  |  |  |  |  |  |  |  |  |  |  | VREG-12370 |  |  | +12v
U4 | ATMEGA328P_TQFP | ATMEGA328P_TQFP | TQFP32-08 | Popular 328P in QFP |  |  |  |  |  |  |  |  |  |  |  | IC-09069 |  |  | ATMEGA328P_TQFP
U5 | ATMEGA328P_TQFP | ATMEGA328P_TQFP | TQFP32-08 | Popular 328P in QFP |  |  |  |  |  |  |  |  |  |  |  | IC-09069 |  |  | ATMEGA328P_TQFP

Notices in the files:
parts and their libraries:
SparkFun-Capacitors: Licensing: Creative Commons ShareAlike 4.0 International - https://creativecommons.org/licenses/by-sa/4.0
SparkFun-Connectors: Licensing: CC v3.0 Share-Alike You are welcome to use this library for commercial purposes.
